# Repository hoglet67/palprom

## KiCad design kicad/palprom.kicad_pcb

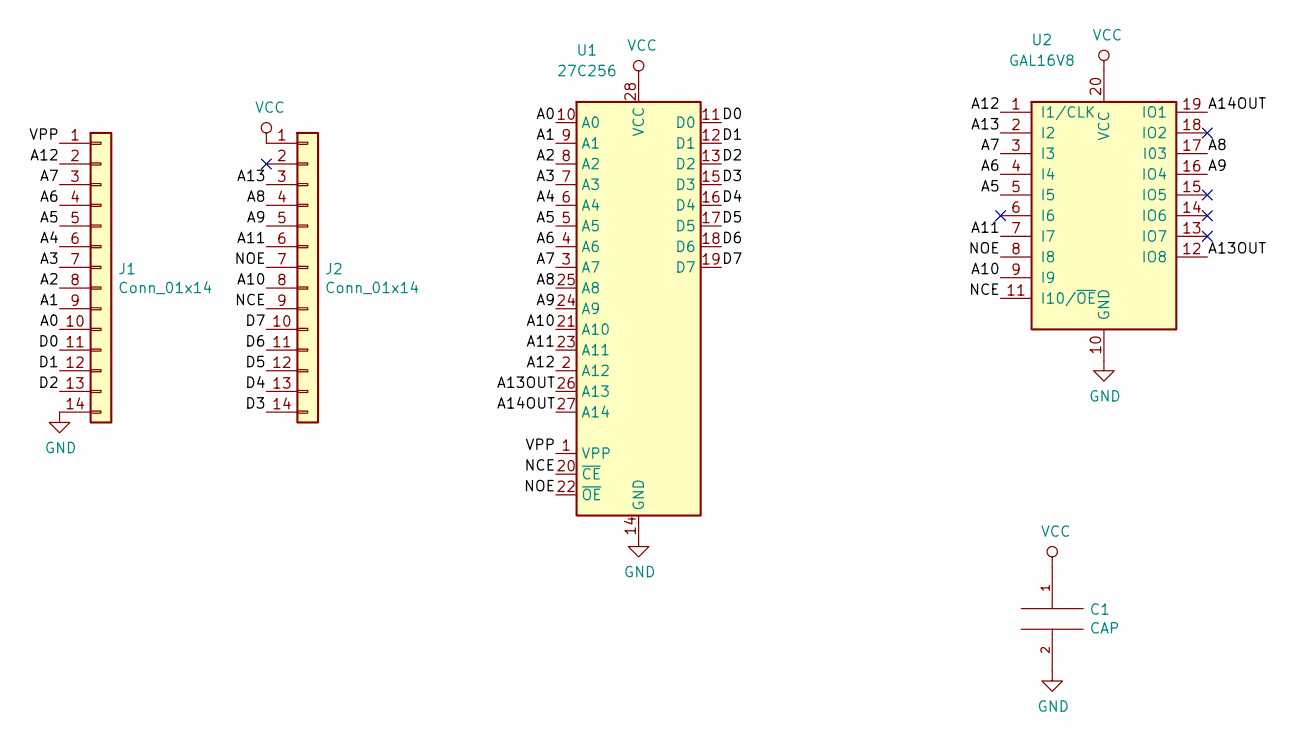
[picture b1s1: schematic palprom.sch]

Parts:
C1: CAP; C_Axial_L3.8mm_D2.6mm_P17.50mm_Horizontal
J1, J2: Conn_01x14; PinHeader_1x14_P2.54mm_Vertical
U1: 27C256; DIP-28_W15.24mm_Socket
U2: GAL16V8; DIP-20_W7.62mm_Socket

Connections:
/A0: J1.10, U1.10 (A0)
/A1: J1.9, U1.9 (A1)
/A2: J1.8, U1.8 (A2)
/A3: J1.7, U1.7 (A3)
/A4: J1.6, U1.6 (A4)
/A5: J1.5, U1.5 (A5), U2.5 (I5)
/A6: J1.4, U1.4 (A6), U2.4 (I4)
/A7: J1.3, U1.3 (A7), U2.3 (I3)
/A8: J2.4, U1.25 (A8), U2.17 (I03)
/A9: J2.5, U1.24 (A9), U2.16 (IO4)
/A10: J2.8, U1.21 (A10), U2.9 (I9)
/A11: J2.6, U1.23 (A11), U2.7 (I7)
/A12: J1.2, U1.2 (A12), U2.1 (I1/CLK)
/A13: J2.3, U2.2 (I2)
/A13OUT: U1.26 (A13), U2.12 (IO8)
/A14OUT: U1.27 (A14), U2.19 (IO1)
/D0: J1.11, U1.11 (D0)
/D1: J1.12, U1.12 (D1)
/D2: J1.13, U1.13 (D2)
/D3: J2.14, U1.15 (D3)
/D4: J2.13, U1.16 (D4)
/D5: J2.12, U1.17 (D5)
/D6: J2.11, U1.18 (D6)
/D7: J2.10, U1.19 (D7)
/NCE: J2.9, U1.20 (~CE), U2.11 (I10/~OE~)
/NOE: J2.7, U1.22 (~OE), U2.8 (I8)
/VPP: J1.1, U1.1 (VPP)
GND: C1.2, J1.14, U1.14 (GND), U2.10 (GND)
VCC: C1.1, J2.1, U1.28 (VCC), U2.20 (VCC)

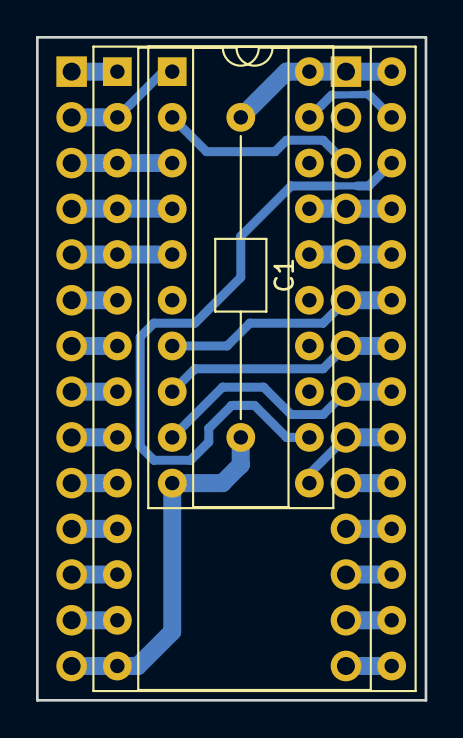
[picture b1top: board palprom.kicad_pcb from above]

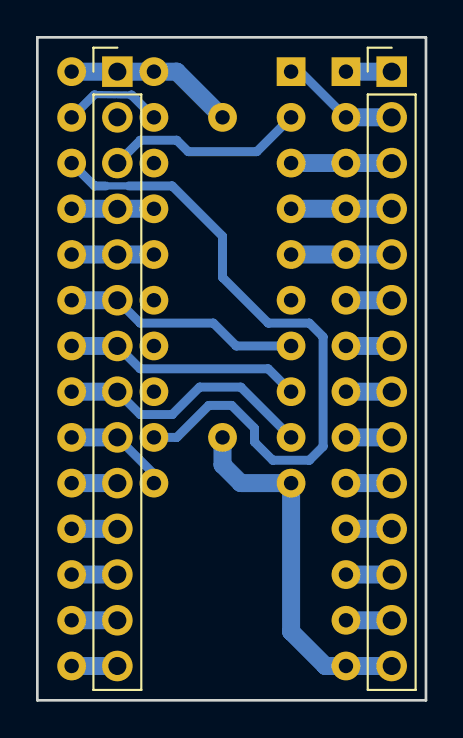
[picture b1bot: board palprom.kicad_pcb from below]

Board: 2 copper layers, 21.6 x 36.8 mm, 5 parts (2 on the bottom side), 29 nets.

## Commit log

2018-10-24 KiCad - initial version for home etching
2018-10-24 PAL - initial version for Quest Paint
2018-10-24 Added roms from IanB
2018-10-24 Added docs from IanB
2018-10-24 Added Quest Paint support disc
2018-10-25 PAL - initial version for Wapping Editor
2023-09-09 PAL - Wapping Editor pinout updated to match original carrier
